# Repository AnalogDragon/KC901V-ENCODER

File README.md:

# KC901V-ENCODER

KC901V顶部的编码器手感十分屎，猜测它设计时仅采用了单边缘计数，另一个边只做了电平判断方向。所以在慢速左右转或者偶然回弹的时候，会有不自然的光标移动。

所以做了一个支持双边缘的编码器模块替换原装的编码器小板子，先让我嚼一遍编码器数据再喂给主板，优化手感与体验。

包含了硬件与软件。  
应该可以用于其他配置的相同外观的KC901x，新版的大约已经修复了相关的问题。

##  

与原小板比较

## 安装

替换原编码器位置，但是因为需要额外的3.3V供电，所以还需要一根飞线将主板的3.3V引上来。

这里使用了一根空中连接的1p杜邦线连接。

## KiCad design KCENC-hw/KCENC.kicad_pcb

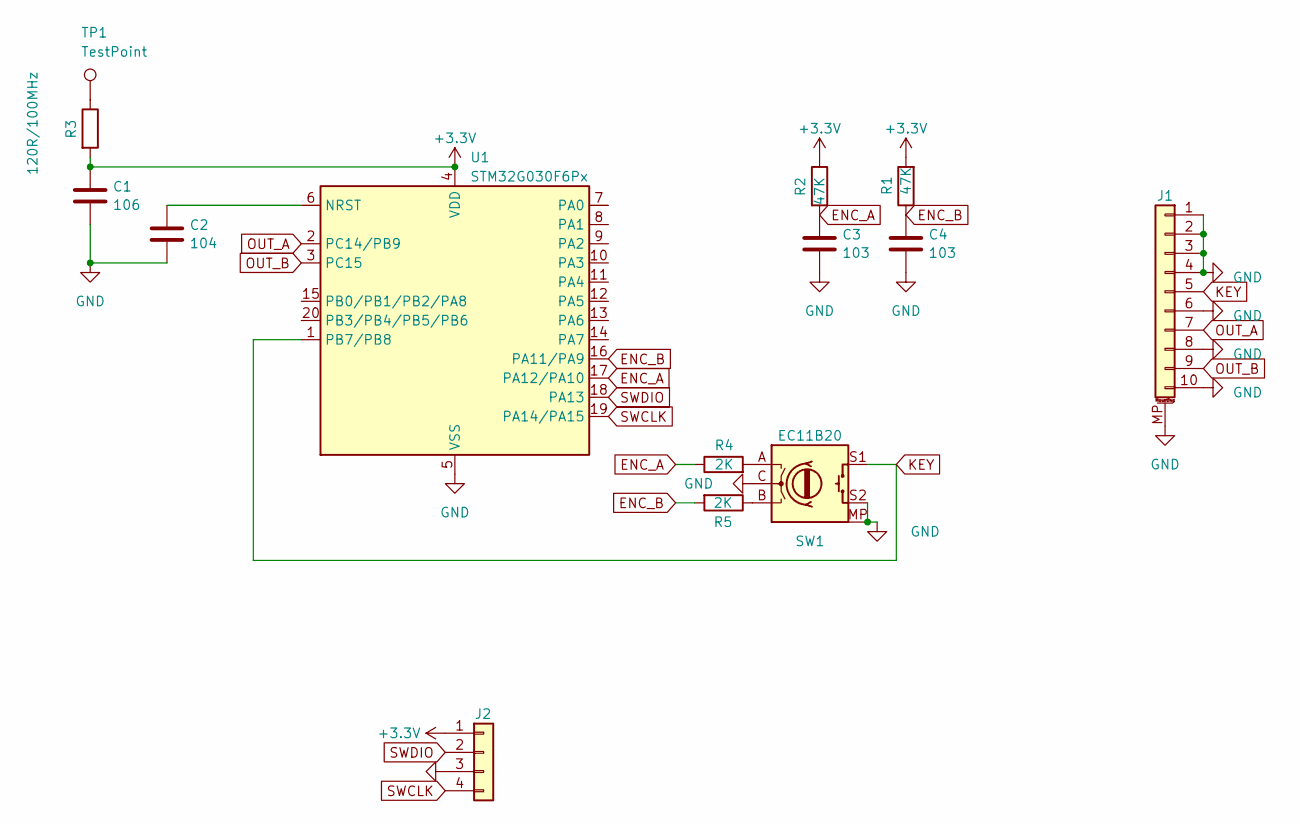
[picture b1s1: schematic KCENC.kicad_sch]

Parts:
C1: 106; C_0603_1608Metric
C2: 104; C_0402_1005Metric
C3, C4: 103; C_0402_1005Metric
J1: Conn_01x10_MountingPin; Molex_200528-0100_1x10-1MP_P1.00mm_Horizontal
J2: Conn_01x04; PinSocket_1x04_P2.00mm_Vertical
R1, R2: 47K; R_0402_1005Metric
R3: 120R/100MHz; C_0402_1005Metric
R4, R5: 2K; R_0402_1005Metric
SW1: EC11B20; RotaryEncoder_Alps_EC11E-Switch_Vertical_H20mm
TP1: TestPoint; TestPoint_Pad_D2.0mm
U1: STM32G030F6Px; TSSOP-20_4.4x6.5mm_P0.65mm

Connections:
+3.3V: C1.1, J2.1, R1.2, R2.1, R3.2, U1.4 (VDD)
ENC_A: C3.1, R2.2, R4.1, U1.17 (PA12/PA10)
ENC_B: C4.1, R1.1, R5.2, U1.16 (PA11/PA9)
GND: C1.2, C2.2, C3.2, C4.2, J1.1, J1.2, J1.3, J1.4, J1.6, J1.8, J1.10, J1.MP (MountPin), J2.3, SW1.C, SW1.MP, SW1.S2, U1.5 (VSS)
KEY: J1.5, SW1.S1, U1.1 (PB7/PB8)
unnamed: R3.1, TP1.1
unnamed: R4.2, SW1.A
unnamed: R5.1, SW1.B
unnamed: C2.1, U1.6 (NRST)
OUT_A: J1.7, U1.2 (PC14/PB9)
OUT_B: J1.9, U1.3 (PC15)
SWCLK: J2.4, U1.19 (PA14/PA15)
SWDIO: J2.2, U1.18 (PA13)

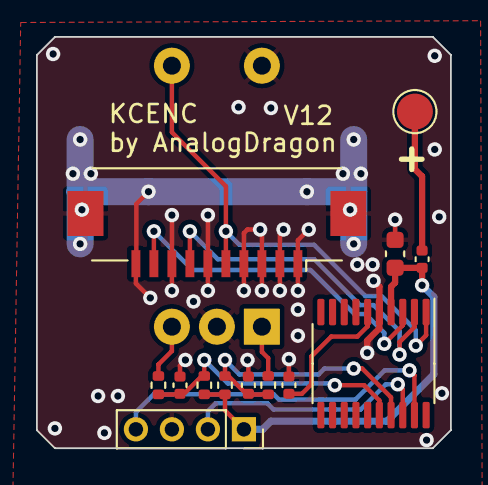
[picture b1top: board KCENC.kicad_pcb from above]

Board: 2 copper layers, 23.0 x 22.9 mm, 14 parts (1 on the bottom side), 13 nets.

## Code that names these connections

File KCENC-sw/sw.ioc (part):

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Mcu.Name=STM32G030F6Px
Mcu.Package=TSSOP20
Mcu.UserName=STM32G030F6Px
PA11\ [PA9].GPIOParameters=GPIO_PuPd,GPIO_Label,GPIO_ModeDefaultEXTI
PA11\ [PA9].GPIO_Label=ENC_B
PA11\ [PA9].GPIO_ModeDefaultEXTI=GPIO_MODE_IT_RISING_FALLING
PA11\ [PA9].GPIO_PuPd=GPIO_PULLUP
PA11\ [PA9].Signal=GPXTI11
PA12\ [PA10].GPIOParameters=GPIO_PuPd,GPIO_Label,GPIO_ModeDefaultEXTI
PA12\ [PA10].GPIO_Label=ENC_A
PA12\ [PA10].GPIO_ModeDefaultEXTI=GPIO_MODE_IT_RISING_FALLING
PA12\ [PA10].GPIO_PuPd=GPIO_PULLUP
PA12\ [PA10].Signal=GPXTI12
PA13.Mode=Serial_Wire
PA13.Signal=SYS_SWDIO
PA14-BOOT0.Mode=Serial_Wire
PA14-BOOT0.Signal=SYS_SWCLK
PA14-BOOT0__PA15.StandardMode=true
PB0__PB1__PB2__PA8.StandardMode=true
PB3__PB4__PB5__PB6.StandardMode=true
PB7.GPIOParameters=GPIO_PuPd,GPIO_Label
PB7.GPIO_Label=KEY
PB7.GPIO_PuPd=GPIO_PULLUP
PB7.Signal=GPIO_Input
PB7__PB8.StandardMode=true
PC14-OSC32_IN\ (PC14).GPIOParameters=PinState,GPIO_PuPd,GPIO_Label,GPIO_ModeDefaultOutputPP
PC14-OSC32_IN\ (PC14).GPIO_Label=OUT_A
PC14-OSC32_IN\ (PC14).GPIO_ModeDefaultOutputPP=GPIO_MODE_OUTPUT_PP
PC14-OSC32_IN\ (PC14).GPIO_PuPd=GPIO_NOPULL
PC14-OSC32_IN\ (PC14).PinState=GPIO_PIN_RESET
PC14-OSC32_IN\ (PC14).Signal=GPIO_Output
PC14-OSC32_IN\ (PC14)__PB9.StandardMode=true
PC15-OSC32_OUT\ (PC15).GPIOParameters=PinState,GPIO_Label
PC15-OSC32_OUT\ (PC15).GPIO_Label=OUT_B
PC15-OSC32_OUT\ (PC15).PinState=GPIO_PIN_RESET
PC15-OSC32_OUT\ (PC15).Signal=GPIO_Output
RCC.HSE_VALUE=8000000
RCC.SYSCLKFreq_VALUE=64000000
RCC.SYSCLKSource=RCC_SYSCLKSOURCE_PLLCLK
board=custom
